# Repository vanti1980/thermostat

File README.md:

# thermostat
Smart thermostat implementation using Raspberry Pico W

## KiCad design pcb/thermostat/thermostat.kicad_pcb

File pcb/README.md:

# Clone the following libs into the library folder
https://github.com/pforrmi/KiCad-SSD1306-128x64

# Set KICAD_LIB_HOME env. variable to the library folder

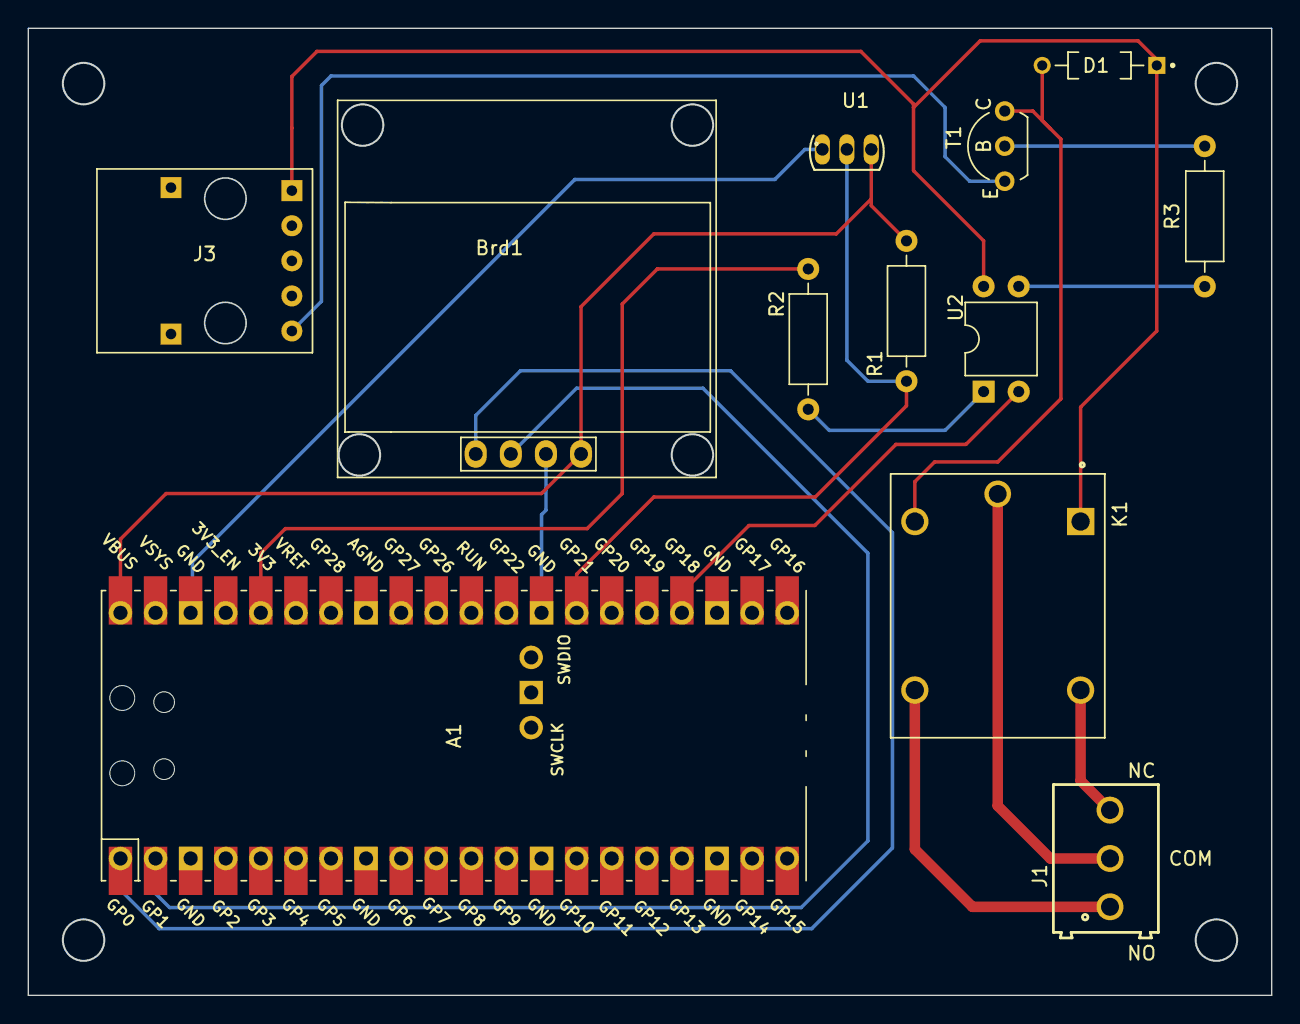
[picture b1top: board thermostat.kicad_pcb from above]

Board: 2 copper layers, 89.9 x 69.9 mm, 12 parts (0 on the bottom side), 16 nets.

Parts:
A1: RaspberryPi-PicoW; RPi_PicoW_SMD_TH
Brd1: SSD1306; 128x64OLED
D1: 1N4148; DIOAD829W49L456D191
J1: 691214110003
J3: USB_B_Micro; MICROUSB-DIP5
K1: SRD-05VDC-SL-C; RELAY_SRD-05VDC-SL-C
R1: R4,7K; R_Axial_DIN0207_L6.3mm_D2.5mm_P10.16mm_Horizontal
R2: R1K; R_Axial_DIN0207_L6.3mm_D2.5mm_P10.16mm_Horizontal
R3: R510; R_Axial_DIN0207_L6.3mm_D2.5mm_P10.16mm_Horizontal
T1: 2N4401; TO92-CBE
U1: DS18B20; TO-92
U2: LTV-817; DIP-4_W7.62mm

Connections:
/MicroUSB connector/VBUS: D1.C, J3.1 (VBUS), U2.4
GND: A1.3 (GND), A1.8 (GND), A1.13 (GND), A1.18 (GND), A1.23 (GND), A1.28 (GND), A1.38 (GND), Brd1.2 (GND), U1.1 (GND)
GND2: J3.5 (GND), T1.E
unnamed: A1.1 (GPIO0), Brd1.4 (SDA)
unnamed: A1.2 (GPIO1), Brd1.3 (SCL)
unnamed: A1.24 (GPIO18), U2.2
unnamed: A1.27 (GPIO21), R1.2, U1.2 (DQ)
unnamed: A1.36 (3V3), R2.1
unnamed: A1.40 (VBUS), Brd1.1 (VCC), R1.1, U1.3 (VDD)
unnamed: K1.A2, T1.C
unnamed: J1.2, K1.COM
unnamed: J1.3, K1.NC
unnamed: J1.1, K1.NO
unnamed: R2.2, U2.1
unnamed: R3.1, U2.3
unnamed: R3.2, T1.B

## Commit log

2022-10-01 Using npm instead of yarn
2022-10-01 After npm upgrade
2022-10-01 Repo fixed
2022-10-04 Initial try
2022-10-04 (fix) Fix imports
2022-10-04 (fix) Fix const order
2022-10-04 (fix) Enable plain text contents
2022-10-04 (fix) Typo
2022-10-04 (fix) createId fix
2022-10-04 (fix) DB initialization
2022-10-04 (fix) Cyclic-DynamoDB import
2022-10-04 (fix) CyclicDB Access try #2
2022-10-04 (feature) Status handling added and some schedule stuff, as well
2022-10-04 (fix) Get schedule fix
2022-10-23 (refactor) Refactor using NX and NestJS
2022-10-23 (feat) First try to deploy with NX
2022-10-30 feat: Moved to pure TS and Vue because of smaller footprint
2022-10-30 fix: Build prior to start
2022-11-24 feat: First working version with Vue
2022-11-26 feat: Schedule ordering
2022-11-26 feat: Calendar view added
2022-12-11 feat: Calendar events added
2022-12-12 fix: Start script fix
2022-12-12 fix: start script fix?
2022-12-12 fix: Primeflex added to avoid CORS problem
2022-12-12 fix: package-lock
2023-01-22 consider 'all' as default schedule status filter
2023-01-22 fix: Sort statuses by descending timestamp
2023-01-22 fix: Sort schedules by priority
2023-01-22 fix: Delete dist folder content prior to build
2023-01-22 chore: Turn on verbose logging to check why build fails
2023-01-22 chore: Packages updated
2023-01-22 chore: verbose build removed
2023-01-22 fix: Relative path for main.js
2023-01-22 fix: Try to use index.js with reference to dist
2023-01-25 feat: RPi code 1st commit
2023-04-01 PCB and rPi Pico app added
2023-04-01 Fix if temp value is just equal than set +- hysteresis

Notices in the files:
pcb/thermostat/thermostat.kicad_pcb:
creativecommons.org/licenses/by/4.0
License: CC BY 4.0
